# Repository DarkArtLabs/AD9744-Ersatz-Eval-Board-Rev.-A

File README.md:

# AD9744 Ersatz Eval Board
A low-cost evaluation board for the Analog Devices [AD9744](https://www.analog.com/en/products/ad9744.html) 14-bit DAC.

The ersatz evaluation board is a low-cost alternative to the AD9744-FMC-EBZ evaluation board produced by Analog Devices which retails for approximately $500. The full BOM cost for this project including components, the board itself, tax, and shipping is about $100. 
The area of the PCB is 23 cm<sup>2</sup> and it is designed to be built on standard 2-layer FR4 by any PCB fabricator. All components sit on the top of the board and the design is hand-solderable. 

# Features
  - Power the board through pin header, terminal block, or separately power analog and digital sections
  - Select 2's complement or unsigned binary DAC word using a jumper
  - External clock input
  - 50 Ohm output impedance
  - Test points on DAC output before balun
  - Mounting holes for M2 hardware or standoffs

# What's Included
Downloads are available below for those who wish to make their own ersatz eval board. The KiCAD project files are also available for those who wish to modify the design. 

## Schematic
The schematic may also be viewed above in the Documents directory.

## Bill of Materials
The BOM may also be viewed above in the Documents directory. It contains manufacturer part numbers and quantities for every component. It also contains Mouser part numbers for easy cross reference. The BOM may be uploaded to the Mouser website and a shopping cart with correct quantities will automatically be generated. Parts may be substituted as long as they meet the minimum tolerances and footprint dimensions. 

To open this file with Excel, it is recommended to import the CSV data. Simply opening the file with Excel will cause formatting errors. 

## Gerbers, Drill File, Drill Map
These files have been generated according to the specifications that JLCPCB requires, but they will likely work at other fabricators such as PCBWay or OSHPARK.

## User Guide
The user guide may also be viewed above in the Documents directory. It contains information on assembly, I/O ports, and jumper options.

# Performance Characteristics

## Power Dissapation

For AVDD and DVDD rails tied together. Test conditions: $` f_{out} = 26.25 \ [MHz] `$, $` f_{clk} = 210 \ [MHz] `$

<br/>

$$ V_{DD} = 3.3 \ \ [V] $$

$$ I_{DD} = 65 \ \ [mA] $$

$$ P_{diss} = 215 \ \ [mW] $$

## S-Parameters & Return Loss

Vout S11: 10 MHz - 100 MHz 

Vout S11: 10 MHz - 100 MHz (markers every 10 MHz)

Vout Return Loss: 10 MHz - 100 MHz (markers every 10 MHz)

## Output Power

26.25 MHz Single Tone (210 MSPS): 0 dBm

# Downloads

Schematic: 

Gerbers: 

BOM: 

User Guide:

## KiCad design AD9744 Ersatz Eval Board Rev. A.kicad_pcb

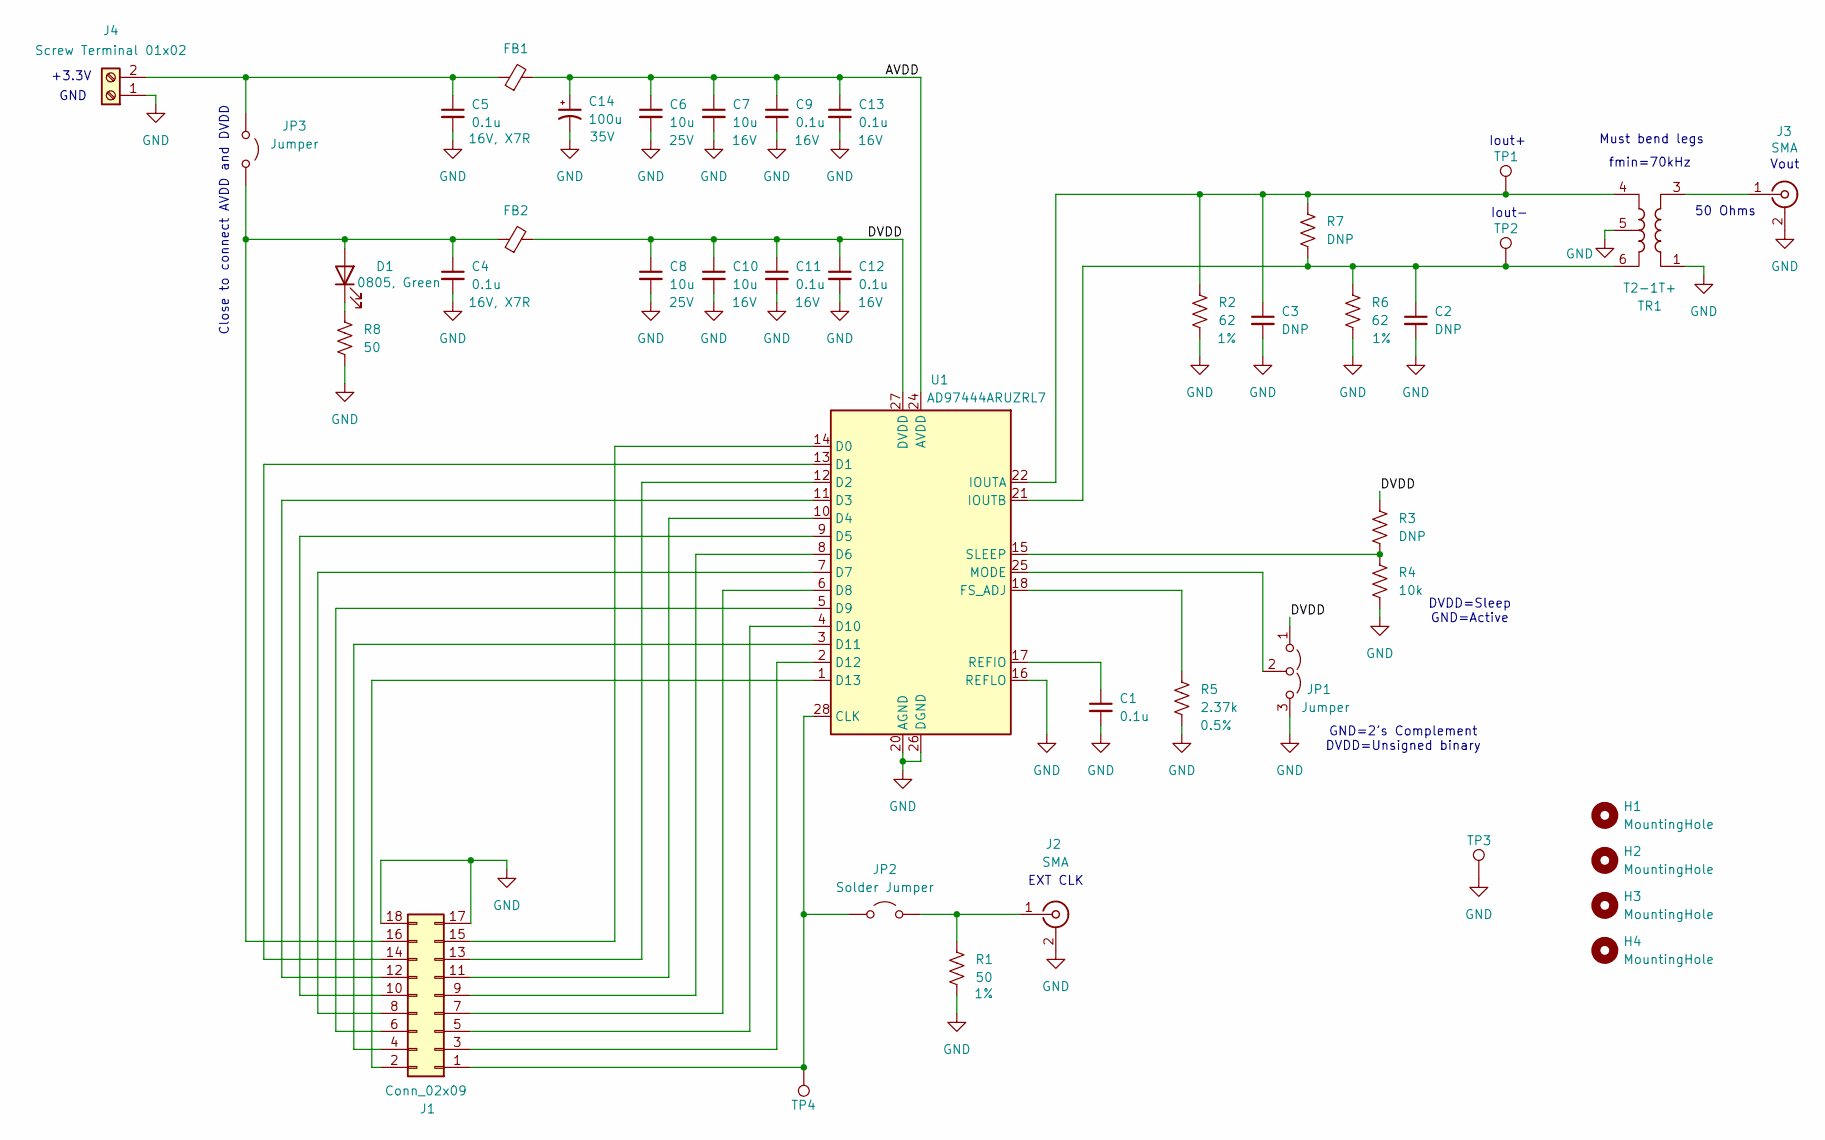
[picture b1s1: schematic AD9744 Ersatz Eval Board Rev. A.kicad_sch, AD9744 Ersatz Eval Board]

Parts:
C1, C4, C5, C9, C11, C12, C13: 0.1u; C_0603_1608Metric_Pad1.08x0.95mm_HandSolder
C2, C3: DNP; C_0603_1608Metric_Pad1.08x0.95mm_HandSolder
C6, C7, C8, C10: 10u; C_0603_1608Metric_Pad1.08x0.95mm_HandSolder
C14: 100u; C_Elec_6.3x7.7
D1: AP2012SGD3; LED_0805_2012Metric_Pad1.15x1.40mm_HandSolder
FB1, FB2: BLM18KN601EH1D; L_0603_1608Metric_Pad1.05x0.95mm_HandSolder
H1, H2, H3, H4: MountingHole; MountingHole_2.2mm_M2_DIN965_Pad
J1: Conn_02x09; PinHeader_2x09_P2.54mm_Vertical
J2, J3: SMA; SMA_Amphenol_901-144_Vertical
J4: Screw Terminal 01x02; TerminalBlock_Phoenix_MKDS-1,5-2-5.08_1x02_P5.08mm_Horizont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
JP1: Jumper; PinHeader_1x03_P2.54mm_Vertical
JP2: Solder Jumper; SolderJumper-2_P1.3mm_Open_RoundedPad1.0x1.5mm
JP3: Jumper; PinHeader_1x02_P2.54mm_Vertical
R1, R8: 50; R_0603_1608Metric_Pad0.98x0.95mm_HandSolder
R2, R6: 62; R_0603_1608Metric_Pad0.98x0.95mm_HandSolder
R3, R7: DNP; R_0603_1608Metric_Pad0.98x0.95mm_HandSolder
R4: 10k; R_0603_1608Metric_Pad0.98x0.95mm_HandSolder
R5: 2.37k; R_0603_1608Metric_Pad0.98x0.95mm_HandSolder
TP1, TP2, TP3, TP4: TestPoint_Keystone_5000-5004_Miniature
TR1: T2-1T+; DIP-6_W7.62mm
U1: AD97444ARUZRL7; TSSOP-28_4.4x9.7mm_P0.65mm

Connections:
/AVDD: C6.1, C7.1, C9.1, C13.1, C14.1, FB1.2, U1.24 (AVDD)
/DVDD: C8.1, C10.1, C11.1, C12.1, FB2.2, JP1.1 (A), R3.1, U1.27 (DVDD)
GND: C1.2, C2.2, C3.2, C4.2, C5.2, C6.2, C7.2, C8.2, C9.2, C10.2, C11.2, C12.2, C13.2, C14.2, J1.17, J1.18, J2.2 (Ext), J3.2 (Ext), J4.1, JP1.3 (B), R1.2, R2.2, R4.2, R5.2, R6.2, R8.2, TP3.1, TR1.1, TR1.5, U1.16 (REFLO), U1.20 (AGND), U1.26 (DGND)
unnamed: C4.1, D1.2 (A), FB2.1, J1.16, JP3.2 (B)
unnamed: D1.1 (K), R8.1
unnamed: J1.1, JP2.1 (A), TP4.1, U1.28 (CLK)
unnamed: J1.2, U1.1 (D13)
unnamed: J1.3, U1.2 (D12)
unnamed: J1.4, U1.3 (D11)
unnamed: J1.5, U1.4 (D10)
unnamed: J1.6, U1.5 (D9)
unnamed: J1.7, U1.6 (D8)
unnamed: J1.8, U1.7 (D7)
unnamed: J1.9, U1.8 (D6)
unnamed: J1.10, U1.9 (D5)
unnamed: J1.11, U1.10 (D4)
unnamed: J1.12, U1.11 (D3)
unnamed: J1.13, U1.12 (D2)
unnamed: J1.14, U1.13 (D1)
unnamed: J1.15, U1.14 (D0)
unnamed: J2.1 (In), JP2.2 (B), R1.1
unnamed: J3.1 (In), TR1.3
unnamed: C5.1, FB1.1, J4.2, JP3.1 (A)
unnamed: JP1.2 (C), U1.25 (MODE)
unnamed: R5.1, U1.18 (FS_ADJ)
unnamed: C3.1, R2.1, R7.1, TP1.1, TR1.4, U1.22 (IOUTA)
unnamed: C2.1, R6.1, R7.2, TP2.1, TR1.6, U1.21 (IOUTB)
unnamed: C1.1, U1.17 (REFIO)
unnamed: R3.2, R4.1, U1.15 (SLEEP)

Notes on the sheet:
fmin=70kHz
Vout
EXT CLK
DVDD=Sleep GND=Active
Iout+
Close to connect AVDD and DVDD
+3.3V
GND=2's Complement DVDD=Unsigned binary
GND
Iout-
Must bend legs
50 Ohms

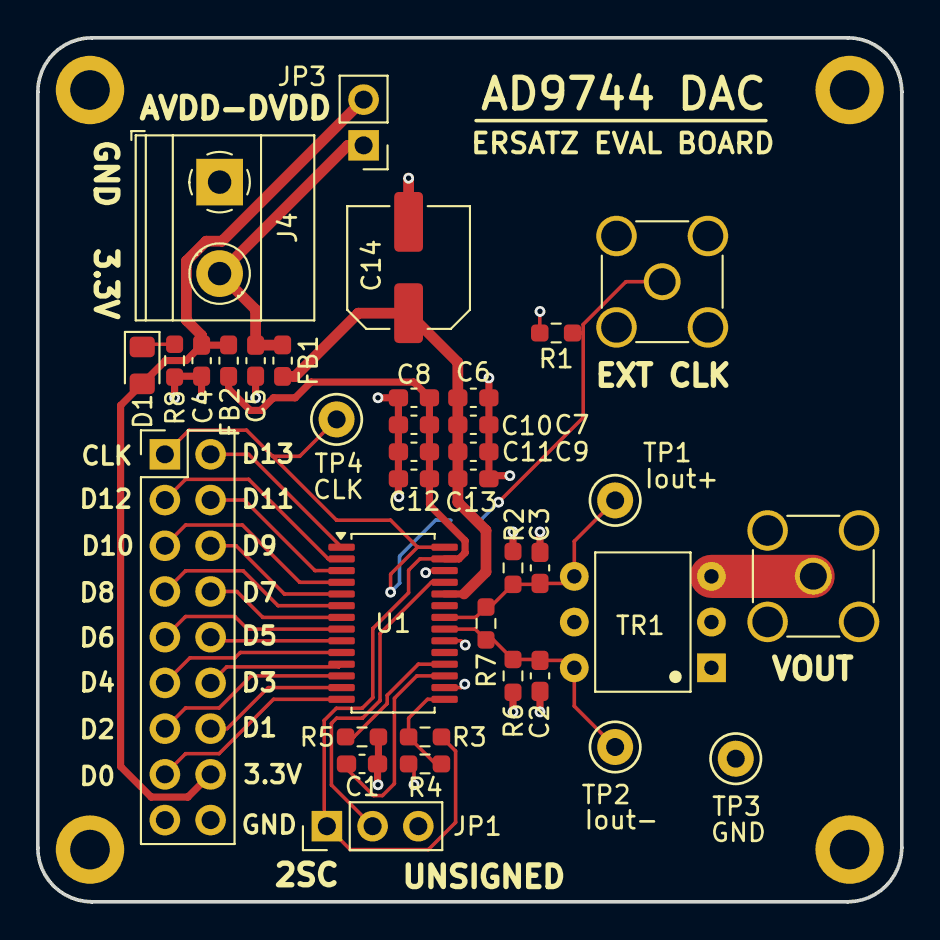
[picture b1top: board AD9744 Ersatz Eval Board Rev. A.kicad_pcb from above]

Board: 2 copper layers, 48.0 x 48.0 mm, 42 parts (1 on the bottom side), 29 nets.

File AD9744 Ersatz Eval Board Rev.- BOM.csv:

Item #,Qty,Ref Des,Manufacturer,Manufacturer Part Number,Description,Package,Type,Location
1,1,U1,Analog Devices,AD9744ARUZRL7 ,14 Bit DAC; 210 MSPS,TSSOP-28,SMT,Top
2,1,TR1,Mini Circuits,T1-6T+,Balun; 1:1,W38,SMT,Top
3,1,J1,Adam Tech,PH2-18-UA ,Pin Header; 2.54mm pitch; 2x9; Male,,Thru-Hole,Top
4,1,JP1,Adam Tech,PH1-03-UA ,Pin Header; 2.54mm pitch; 1x3; Male,,Thru-Hole,Top
5,1,JP3,Adam Tech,PH1-02-UA ,Pin Header; 2.54mm pitch; 1x2; Male,,Thru-Hole,Top
6,2,"J2, J3",Amphenol,901-144 ,SMA Connector; Female; Vertical; 5.08 pitch,,Thru-Hole,Top
7,1,J4,Keystone,8738,2 Pos Terminal Block; Screw Type; 5.08mm pitch; Blue,,Thru-Hole,Top
8,1,D1,Wurth,150224BS73100 ,Blue LED,0805,SMT,Top
9,2,"FB1, FB2",Murata,BLM18KN601EH1D ,Ferrite Bead,0603,SMT,Top
10,1,C14,Wurth,865080545012,Electrolytic Capacitor; 100uF; 35VDC,6.3mm,SMT,Top
11,2,"C7, C10",Kyocera,0603YD106MAT2A ,MLCC 10uF; 16VDC; X5R,0603,SMT,Top
12,2,"C6, C8",Murata,GRM188R61E106KA73J ,MLCC 10uF; 25VDC; X5R,0603,SMT,Top
13,7,"C1, C4, C5, C9, C11, C12, C13",Kyocera,KAM15AR71C104KM ,MLCC; 0.1uF; 16VDC; X7R,0603,SMT,Top
14,4,"R1, R2, R6",Yageo,AT0603DRD0749R9L ,50 Ohm; 1%,0603,SMT,Top
15,1,R5,Panasonic,ERA-3AED202V ,2k Ohm; 1%,0603,SMT,Top
16,1,R4,Vishay,CRCW060310K0FKEI ,10k Ohm; 5%,0603,SMT,Top
17,1,R8,Vishay,CRCW060313R0JNEA ,"13 Ohm, 5%",0603,SMT,Top
18,3,"TP1, TP2, TP4",Keystone,5002,Mini Loop Test Point; White,,Thru-Hole,Top
19,1,TP3,Keystone,5001,Mini Loop Test Point; Black,,Thru-Hole,Top

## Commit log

2025-01-01 Add BOM
2025-01-01 Update README.md
    fixed title
2025-01-01 Update AD9744 Ersatz Eval Board Rev.A BOM.csv
    Updates to file name
2025-01-01 added Document dir
2025-01-01 added schematic
2025-01-01 updated schematic
2025-01-01 added gerbers
2025-01-01 BOM update
2025-01-01 fixed BOM .CSV formatting
2025-01-01 added pics
2025-01-01 bom changes
2025-01-01 bom line changes
2025-01-02 updates to ref des on schema
2025-01-02 Create Assembly and User Guide
2025-01-02 Rename Assembly and User Guide to AD9744 Ersatz Eval Board Rev. AAssembly and User Guide
2025-01-02 Rename AD9744 Ersatz Eval Board Rev. AAssembly and User Guide to AD9744 Ersatz Eval Board Rev. A Assembly and User Guide
2025-01-02 Rename AD9744 Ersatz Eval Board Rev. A Assembly and User Guide to AD9744 Ersatz Eval Board Rev. A Assembly and User Guide.md
2025-01-03 TR1 pad changes
2025-01-03 new TR1 footprint
2025-01-03 changes for TR1
2025-01-04 tr1 footprint change
2025-01-04 TR1 silkscreen change
2025-01-05 new 3D renders
2025-01-05 diagram updates
2025-01-05 Rename AD9744 Ersatz Eval Board Rev. A Back Copper.png to AD9744 Ersatz Eval Board Rev. A Copper Back.png
2025-01-05 Rename AD9744 Ersatz Eval Board Rev. A Front Copper.png to AD9744 Ersatz Eval Board Rev. A Copper Front.png
2025-01-05 Rename AD9744 Ersatz Eval Board Rev. A Front.png to AD9744 Ersatz Eval Board Rev. A Layout Front.png
2025-01-05 Rename AD9744 Ersatz Eval Board Rev. A Back.png to AD9744 Ersatz Eval Board Rev. A Layout Back.png
2025-01-05 added 9744 datasheet
2025-01-05 3D render updates
2025-01-05 fixed schema links
2025-01-05 new pics
2025-01-05 zip gerbers
2025-01-05 added kicad files
2025-01-06 test
2025-01-06 new renders
2025-01-06 new render
2025-01-06 kicad checks
2025-01-07 fixed LED color
2025-01-07 fixed error in schema note
2025-01-17 R value changes, removed old schema notes, added s-params
2025-01-17 clean up
2025-01-17 added s-parameter pics
2025-01-17 added Pout measurements
2025-01-17 fixed file name
2025-01-17 Release A1
2025-01-17 backups
